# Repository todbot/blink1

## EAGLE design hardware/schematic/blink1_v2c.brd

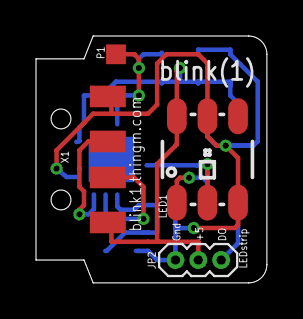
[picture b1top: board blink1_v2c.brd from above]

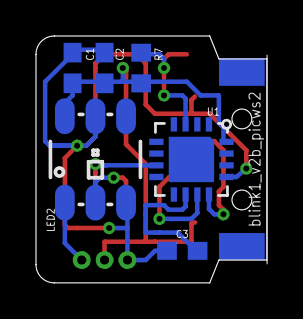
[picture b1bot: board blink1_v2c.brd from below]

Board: 2 copper layers, 12.8 x 13.7 mm, 10 parts (6 on the bottom side), 9 nets.

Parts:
C1, C3: 100nF; C0603
C2: 10uF; C0603
JP2: M03; 1X03-1.27MM
LED1, LED2: LED-TRICOLOR-5050-ICWS2811; LED-TRICOLOR-5050-IC
P1: TPTP11SQ; TP11SQ
R7: 10k; R0603
U1: PIC16F1455ML; QFN16_4X4
X1: USB; MOLEX-48037-1000

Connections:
+5V: C1.1, C2.1, JP2.2, LED1.6, LED2.6, R7.2, U1.16, X1.1
D+: U1.12, X1.3
D-: U1.11, X1.2
DI: LED1.2, U1.7
DO: JP2.1, LED2.1
GND: C1.2, C2.2, C3.2, JP2.3, LED1.3, LED1.5, LED2.3, LED2.5, U1.13, X1.4
unnamed: LED1.1, LED2.2
VPP: P1.TP, R7.1, U1.3
VUSB3V3: C3.1, U1.10

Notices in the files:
parts and their libraries:
SparkFun-LED: Licensing: CC v3.0 Share-Alike You are welcome to use this library for commercial purposes.
